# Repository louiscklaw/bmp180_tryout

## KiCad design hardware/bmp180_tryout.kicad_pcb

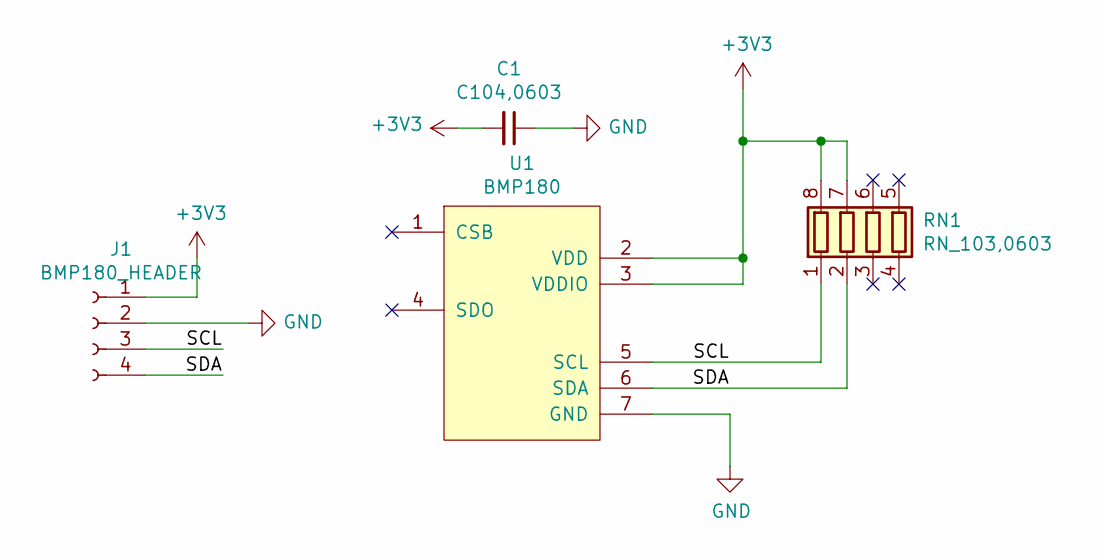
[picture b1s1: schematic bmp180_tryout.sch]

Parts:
C1: C104,0603; C_0603_1608Metric_Pad1.05x0.95mm_HandSolder
J1: BMP180_HEADER; PinHeader_1x04_P1.27mm_Vertical
RN1: RN_103,0603; R_Array_Concave_4x0603
U1: BMP180

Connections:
+3V3: C1.2, J1.1, RN1.7 (R2.2), RN1.8 (R1.2), U1.2 (VDD), U1.3 (VDDIO)
/SCL: J1.3, RN1.1 (R1.1), U1.5 (SCL)
/SDA: J1.4, RN1.2 (R2.1), U1.6 (SDA)
GND: C1.1, J1.2, U1.7 (GND)

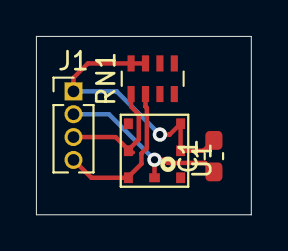
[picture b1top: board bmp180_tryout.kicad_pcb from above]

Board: 2 copper layers, 11.9 x 9.9 mm, 4 parts (0 on the bottom side), 4 nets.

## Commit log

2019-06-26 update,
2020-05-05 ci: init travis build config,
2020-05-05 ci: init travis token,
